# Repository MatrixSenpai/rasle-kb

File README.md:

# Rasle-KB

A [Sofle Choc](https://github.com/josefadamcik/SofleKeyboard) inspired keyboard featuring a 6x4+5 staggered key layout with onboard RP2040 MCU.

## Features:
- Onboard RP2040
- Per-Switch LED backlighting
- [Japanese Duplex Matrix](https://kbd.news/The-Japanese-duplex-matrix-1391.html) design
- RST/BootSel switches
- Onboard, accessible debug port
- Reversible design

Future features:
- Horizontal rotary encoder
- Display
- Wireless support + battery
- RP2350 variant

Planned support for QMK + ZMK, with first-party support for custom, developer-written firmware based on [Embassy](https://embassy.dev/)

Hardware and PCB design is licensed under CC BY-NC-SA. Firmware, software, and any additional non-hardware components are licensed under GNU GPLv3.

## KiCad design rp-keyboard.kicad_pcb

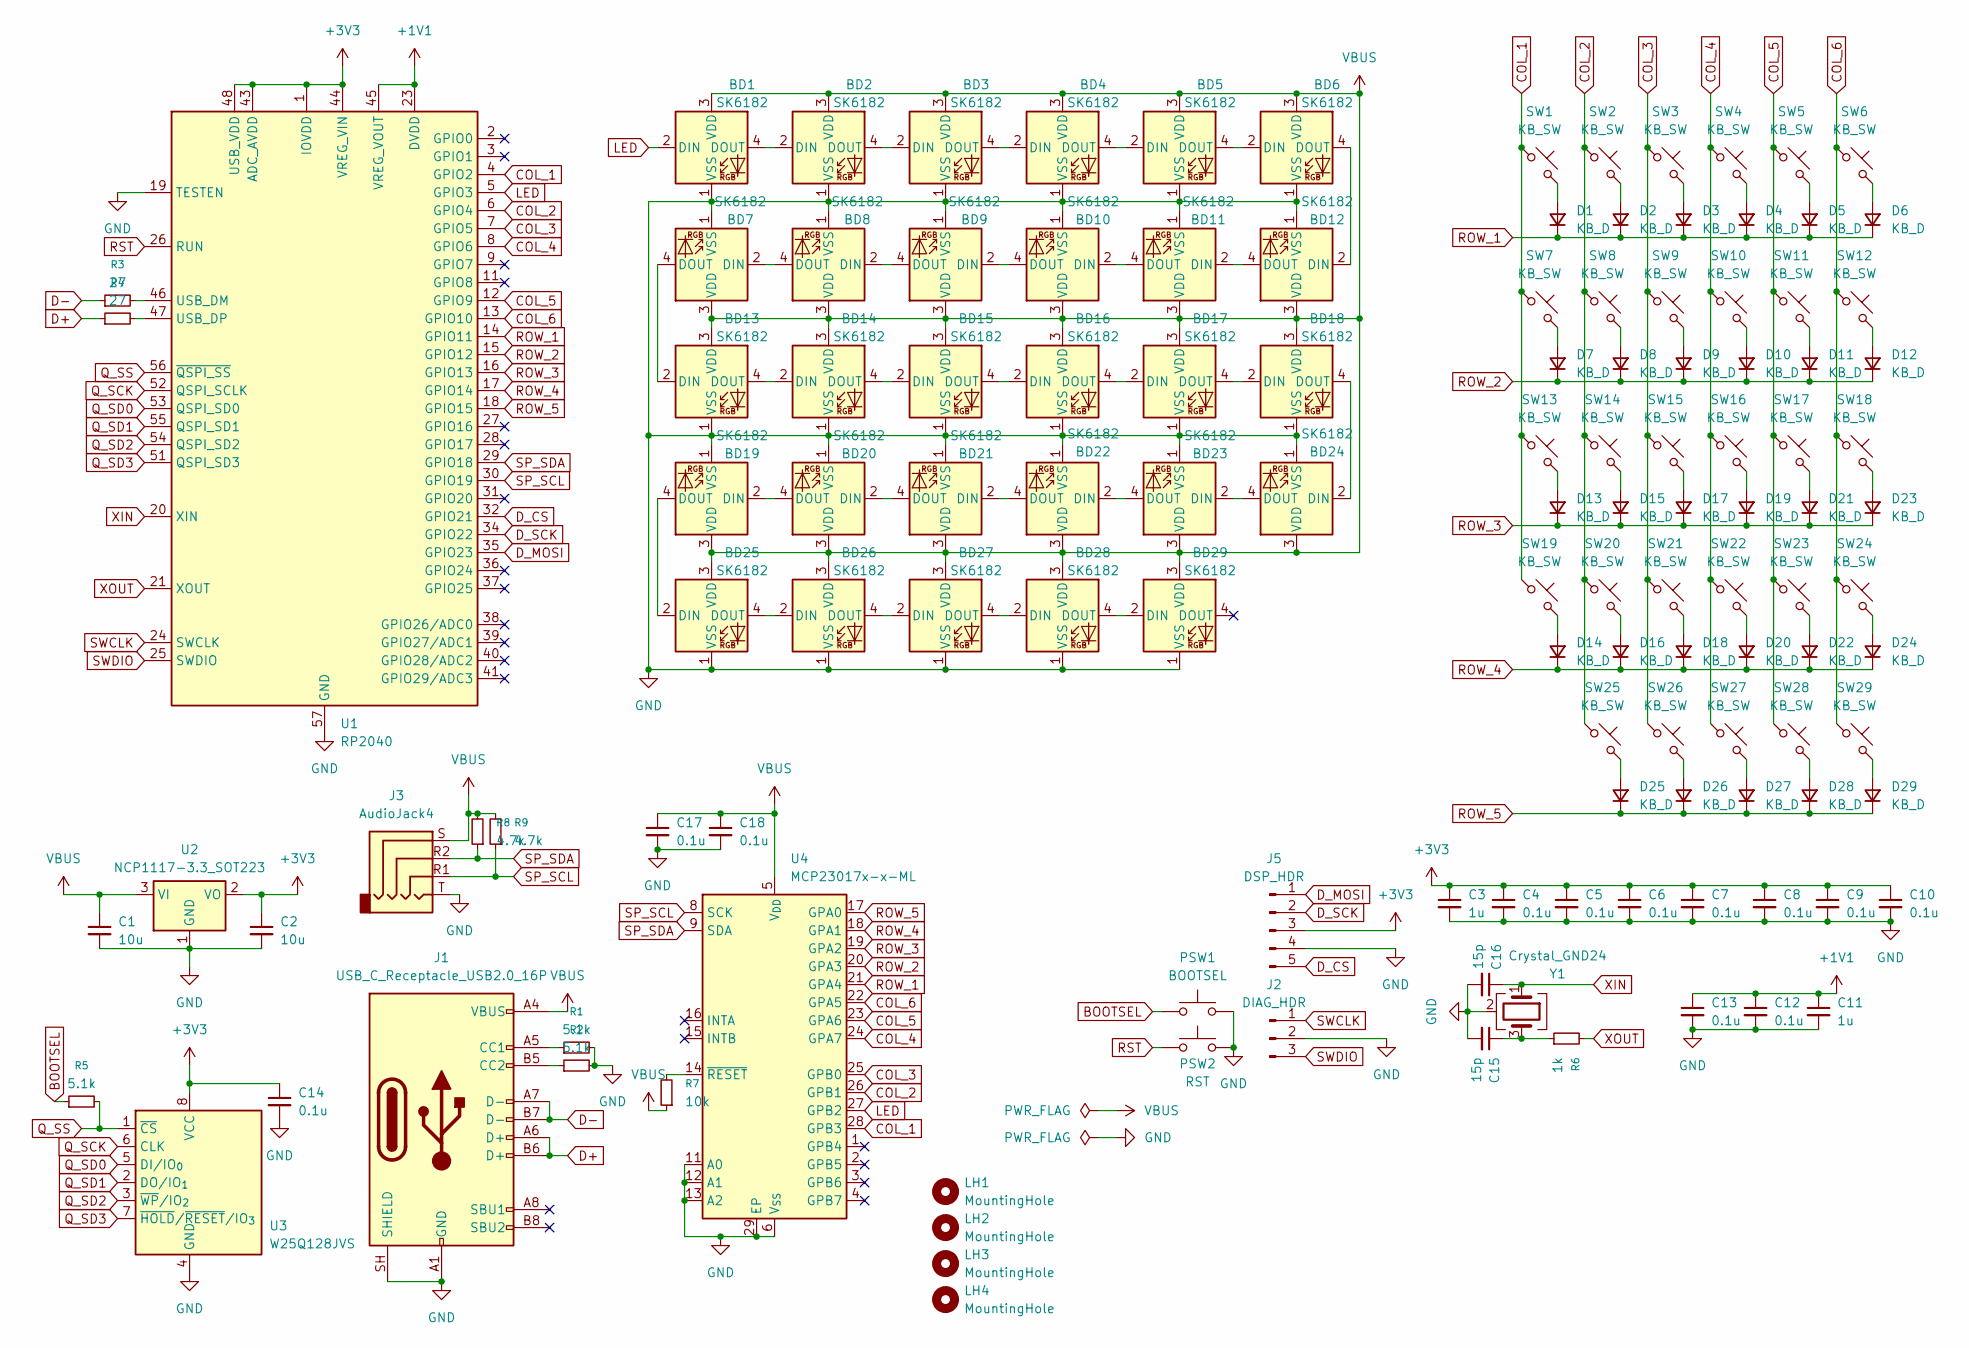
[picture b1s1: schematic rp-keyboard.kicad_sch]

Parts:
BD1, BD2, BD3, BD4, BD5, BD6, BD7, BD8, BD9, BD10, BD11, BD12, BD13, BD14, BD15, BD16, BD17, BD18, BD19, BD20, BD21, BD22, BD23, BD24, BD25, BD26, BD27, BD28, BD29: SK6182; LED_SK6812MINI-E_3.2x2.8mm_P1.5mm_ReverseMount Reversible
C1, C2: 10u; C_0402_1005Metric_Pad0.74x0.62mm_HandSolder
C3, C11: 1u; C_0402_1005Metric_Pad0.74x0.62mm_HandSolder
C4, C5, C6, C7, C8, C9, C10, C12, C13, C14, C17, C18: 0.1u; C_0402_1005Metric_Pad0.74x0.62mm_HandSolder
C15, C16: 15p; C_0402_1005Metric_Pad0.74x0.62mm_HandSolder
D1, D2, D3, D4, D5, D6, D7, D8, D9, D10, D11, D12, D13, D14, D15, D16, D17, D18, D19, D20, D21, D22, D23, D24, D25, D26, D27, D28, D29: KB_D; D_SOD-123 Reversible
J1: USB_C_Receptacle_USB2.0_16P; USB_C_Receptacle_HRO_TYPE-C-31-M-12
J2: DIAG_HDR; PinHeader_1x03_P2.54mm_Vertical
J3: AudioJack4; Jack_3.5mm_KoreanHropartsElec_PJ-320D-4A_Horizontal
J5: DSP_HDR; PinHeader_1x05_P2.54mm_Vertical
LH1, LH2, LH3, LH4: MountingHole; MountingHole_4.3mm_M4
PSW1: BOOTSEL; SW_SPST_SKQG_WithStem
PSW2: RST; SW_SPST_SKQG_WithStem
R1, R2, R5: 5.1k; R_0402_1005Metric_Pad0.72x0.64mm_HandSolder
R3, R4: 27; R_0402_1005Metric_Pad0.72x0.64mm_HandSolder
R6: 1k; R_0402_1005Metric_Pad0.72x0.64mm_HandSolder
R7: 10k; R_0402_1005Metric_Pad0.72x0.64mm_HandSolder
R8, R9: 4.7k; R_0402_1005Metric_Pad0.72x0.64mm_HandSolder
SW1, SW2, SW3, SW4, SW5, SW6, SW7, SW8, SW9, SW10, SW11, SW12, SW13, SW14, SW15, SW16, SW17, SW18, SW19, SW20, SW21, SW22, SW23, SW24, SW25, SW26, SW27, SW28, SW29: KB_SW; SW_Hotswap_Kailh_Choc_V1V2_1.00u Reversible
U1: RP2040; QFN-56-1EP_7x7mm_P0.4mm_EP3.2x3.2mm
U2: NCP1117-3.3_SOT223; SOT-223-3_TabPin2
U3: W25Q128JVS; SOIC-8_5.3x5.3mm_P1.27mm
U4: MCP23017x-x-ML; QFN-28-1EP_6x6mm_P0.65mm_EP4.25x4.25mm
Y1: Crystal_GND24; Crystal_SMD_Abracon_ABM8G-4Pin_3.2x2.5mm

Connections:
+1V1: C11.1, C12.1, C13.1, U1.23 (DVDD), U1.45 (VREG_VOUT), U1.50 (DVDD)
+3V3: C2.1, C3.1, C4.1, C5.1, C6.1, C7.1, C8.1, C9.1, C10.1, C14.1, J5.3, U1.1 (IOVDD), U1.10 (IOVDD), U1.22 (IOVDD), U1.33 (IOVDD), U1.42 (IOVDD), U1.43 (ADC_AVDD), U1.44 (VREG_VIN), U1.48 (USB_VDD), U1.49 (IOVDD), U2.2 (VO), U3.8 (VCC)
BOOTSEL: PSW1.1, R5.1
COL_1: SW1.1, SW7.1, SW13.1, SW19.1, U1.4 (GPIO2), U4.28 (GPB3)
COL_2: SW2.1, SW8.1, SW14.1, SW20.1, SW25.1, U1.6 (GPIO4), U4.26 (GPB1)
COL_3: SW3.1, SW9.1, SW15.1, SW21.1, SW26.1, U1.7 (GPIO5), U4.25 (GPB0)
COL_4: SW4.1, SW10.1, SW16.1, SW22.1, SW27.1, U1.8 (GPIO6), U4.24 (GPA7)
COL_5: SW5.1, SW11.1, SW17.1, SW23.1, SW28.1, U1.12 (GPIO9), U4.23 (GPA6)
COL_6: SW6.1, SW12.1, SW18.1, SW24.1, SW29.1, U1.13 (GPIO10), U4.22 (GPA5)
D+: J1.A6 (D+), J1.B6 (D+), R4.1
D-: J1.A7 (D-), J1.B7 (D-), R3.1
D_CS: J5.5, U1.32 (GPIO21)
D_MOSI: J5.1, U1.35 (GPIO23)
D_SCK: J5.2, U1.34 (GPIO22)
GND: BD1.1 (VSS), BD2.1 (VSS), BD3.1 (VSS), BD4.1 (VSS), BD5.1 (VSS), BD6.1 (VSS), BD7.1 (VSS), BD8.1 (VSS), BD9.1 (VSS), BD10.1 (VSS), BD11.1 (VSS), BD12.1 (VSS), BD13.1 (VSS), BD14.1 (VSS), BD15.1 (VSS), BD16.1 (VSS), BD17.1 (VSS), BD18.1 (VSS), BD19.1 (VSS), BD20.1 (VSS), BD21.1 (VSS), BD22.1 (VSS), BD23.1 (VSS), BD24.1 (VSS), BD25.1 (VSS), BD26.1 (VSS), BD27.1 (VSS), BD28.1 (VSS), BD29.1 (VSS), C1.2, C2.2, C3.2, C4.2, C5.2, C6.2, C7.2, C8.2, C9.2, C10.2, C11.2, C12.2, C13.2, C14.2, C15.2, C16.2, C17.2, C18.2, J1.A1 (GND), J1.A12 (GND), J1.B1 (GND), J1.B12 (GND), J1.SH (SHIELD), J2.2, J3.T, J5.4, PSW1.2, PSW2.2, R1.2, R2.2, U1.19 (TESTEN), U1.57 (GND), U2.1 (GND), U3.4 (GND), U4.6 (V_{SS}), U4.11 (A0), U4.12 (A1), U4.13 (A2), U4.29 (EP), Y1.2 (G), Y1.4 (G)
LED: BD1.2 (DIN), U1.5 (GPIO3), U4.27 (GPB2)
unnamed: BD1.4 (DOUT), BD2.2 (DIN)
unnamed: BD2.4 (DOUT), BD3.2 (DIN)
unnamed: BD3.4 (DOUT), BD4.2 (DIN)
unnamed: BD4.4 (DOUT), BD5.2 (DIN)
unnamed: BD5.4 (DOUT), BD6.2 (DIN)
unnamed: BD7.2 (DIN), BD8.4 (DOUT)
unnamed: BD8.2 (DIN), BD9.4 (DOUT)
unnamed: BD10.2 (DIN), BD11.4 (DOUT)
unnamed: BD9.2 (DIN), BD10.4 (DOUT)
unnamed: BD11.2 (DIN), BD12.4 (DOUT)
unnamed: BD6.4 (DOUT), BD12.2 (DIN)
unnamed: BD7.4 (DOUT), BD13.2 (DIN)
unnamed: BD13.4 (DOUT), BD14.2 (DIN)
unnamed: BD14.4 (DOUT), BD15.2 (DIN)
unnamed: BD15.4 (DOUT), BD16.2 (DIN)
unnamed: BD16.4 (DOUT), BD17.2 (DIN)
unnamed: BD17.4 (DOUT), BD18.2 (DIN)
unnamed: BD18.4 (DOUT), BD24.2 (DIN)
unnamed: BD19.2 (DIN), BD20.4 (DOUT)
unnamed: BD19.4 (DOUT), BD25.2 (DIN)
unnamed: BD20.2 (DIN), BD21.4 (DOUT)
unnamed: BD21.2 (DIN), BD22.4 (DOUT)
unnamed: BD22.2 (DIN), BD23.4 (DOUT)
unnamed: BD23.2 (DIN), BD24.4 (DOUT)
unnamed: BD25.4 (DOUT), BD26.2 (DIN)
unnamed: BD26.4 (DOUT), BD27.2 (DIN)
unnamed: BD27.4 (DOUT), BD28.2 (DIN)
unnamed: BD28.4 (DOUT), BD29.2 (DIN)
unnamed: C15.1, R6.1, Y1.3
unnamed: D1.2 (A), SW1.2
unnamed: D2.2 (A), SW2.2
unnamed: D3.2 (A), SW3.2
unnamed: D4.2 (A), SW4.2
unnamed: D5.2 (A), SW5.2
unnamed: D6.2 (A), SW6.2
unnamed: D7.2 (A), SW7.2
unnamed: D8.2 (A), SW8.2
unnamed: D9.2 (A), SW9.2
unnamed: D10.2 (A), SW10.2
unnamed: D11.2 (A), SW11.2
unnamed: D12.2 (A), SW12.2
unnamed: D13.2 (A), SW13.2
unnamed: D14.2 (A), SW19.2
unnamed: D15.2 (A), SW14.2
unnamed: D16.2 (A), SW20.2
unnamed: D17.2 (A), SW15.2
unnamed: D18.2 (A), SW21.2
unnamed: D19.2 (A), SW16.2
unnamed: D20.2 (A), SW22.2
unnamed: D21.2 (A), SW17.2
unnamed: D22.2 (A), SW23.2
unnamed: D23.2 (A), SW18.2
unnamed: D24.2 (A), SW24.2
unnamed: D25.2 (A), SW25.2
unnamed: D26.2 (A), SW26.2
unnamed: D27.2 (A), SW27.2
unnamed: D28.2 (A), SW28.2
unnamed: D29.2 (A), SW29.2
unnamed: J1.A5 (CC1), R1.1
unnamed: J1.B5 (CC2), R2.1
unnamed: R3.2, U1.46 (USB_DM)
unnamed: R4.2, U1.47 (USB_DP)
unnamed: R7.2, U4.14 (~RESET)
Q_SCK: U1.52 (QSPI_SCLK), U3.6 (CLK)
Q_SD0: U1.53 (QSPI_SD0), U3.5 (DI/IO_{0})
Q_SD1: U1.55 (QSPI_SD1), U3.2 (DO/IO_{1})
Q_SD2: U1.54 (QSPI_SD2), U3.3 (~WP/IO_{2})
Q_SD3: U1.51 (QSPI_SD3), U3.7 (~HOLD/~RESET/IO_{3})
Q_SS: R5.2, U1.56 (~QSPI_SS), U3.1 (~CS)
ROW_1: D1.1 (K), D2.1 (K), D3.1 (K), D4.1 (K), D5.1 (K), D6.1 (K), U1.14 (GPIO11), U4.21 (GPA4)
ROW_2: D7.1 (K), D8.1 (K), D9.1 (K), D10.1 (K), D11.1 (K), D12.1 (K), U1.15 (GPIO12), U4.20 (GPA3)
ROW_3: D13.1 (K), D15.1 (K), D17.1 (K), D19.1 (K), D21.1 (K), D23.1 (K), U1.16 (GPIO13), U4.19 (GPA2)
ROW_4: D14.1 (K), D16.1 (K), D18.1 (K), D20.1 (K), D22.1 (K), D24.1 (K), U1.17 (GPIO14), U4.18 (GPA1)
ROW_5: D25.1 (K), D26.1 (K), D27.1 (K), D28.1 (K), D29.1 (K), U1.18 (GPIO15), U4.17 (GPA0)
RST: PSW2.1, U1.26 (RUN)
SP_SCL: J3.R1, R9.1, U1.30 (GPIO19), U4.8 (SCK)
SP_SDA: J3.R2, R8.1, U1.29 (GPIO18), U4.9 (SDA)
SWCLK: J2.1, U1.24 (SWCLK)
SWDIO: J2.3, U1.25 (SWDIO)
VBUS: BD1.3 (VDD), BD2.3 (VDD), BD3.3 (VDD), BD4.3 (VDD), BD5.3 (VDD), BD6.3 (VDD), BD7.3 (VDD), BD8.3 (VDD), BD9.3 (VDD), BD10.3 (VDD), BD11.3 (VDD), BD12.3 (VDD), BD13.3 (VDD), BD14.3 (VDD), BD15.3 (VDD), BD16.3 (VDD), BD17.3 (VDD), BD18.3 (VDD), BD19.3 (VDD), BD20.3 (VDD), BD21.3 (VDD), BD22.3 (VDD), BD23.3 (VDD), BD24.3 (VDD), BD25.3 (VDD), BD26.3 (VDD), BD27.3 (VDD), BD28.3 (VDD), BD29.3 (VDD), C1.1, C17.1, C18.1, J1.A4 (VBUS), J1.A9 (VBUS), J1.B4 (VBUS), J1.B9 (VBUS), J3.S, R7.1, R8.2, R9.2, U2.3 (VI), U4.5 (V_{DD})
XIN: C16.1, U1.20 (XIN), Y1.1
XOUT: R6.2, U1.21 (XOUT)

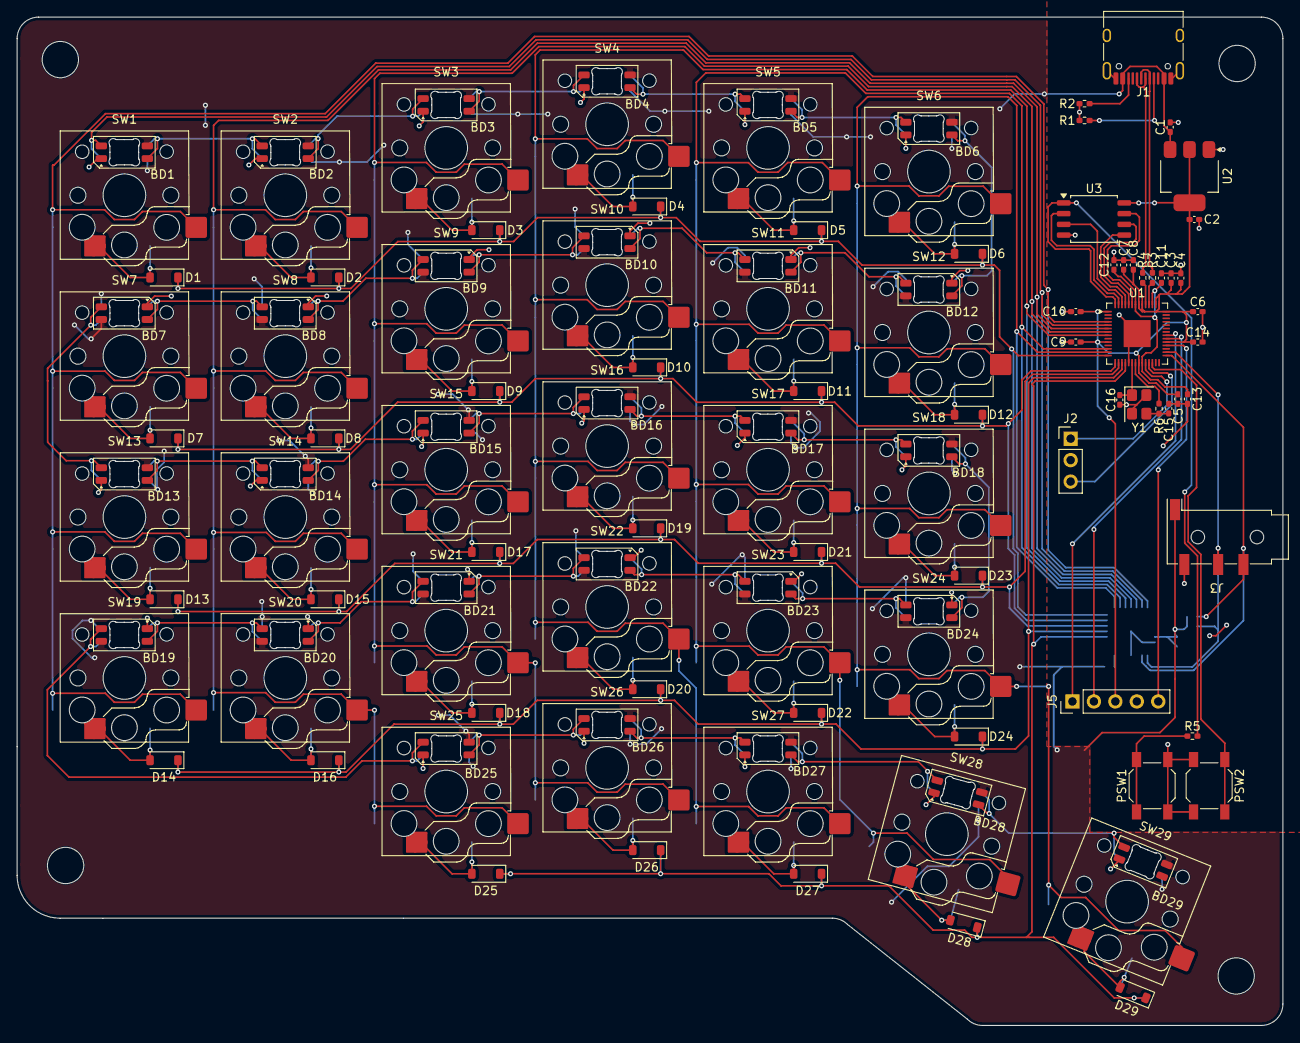
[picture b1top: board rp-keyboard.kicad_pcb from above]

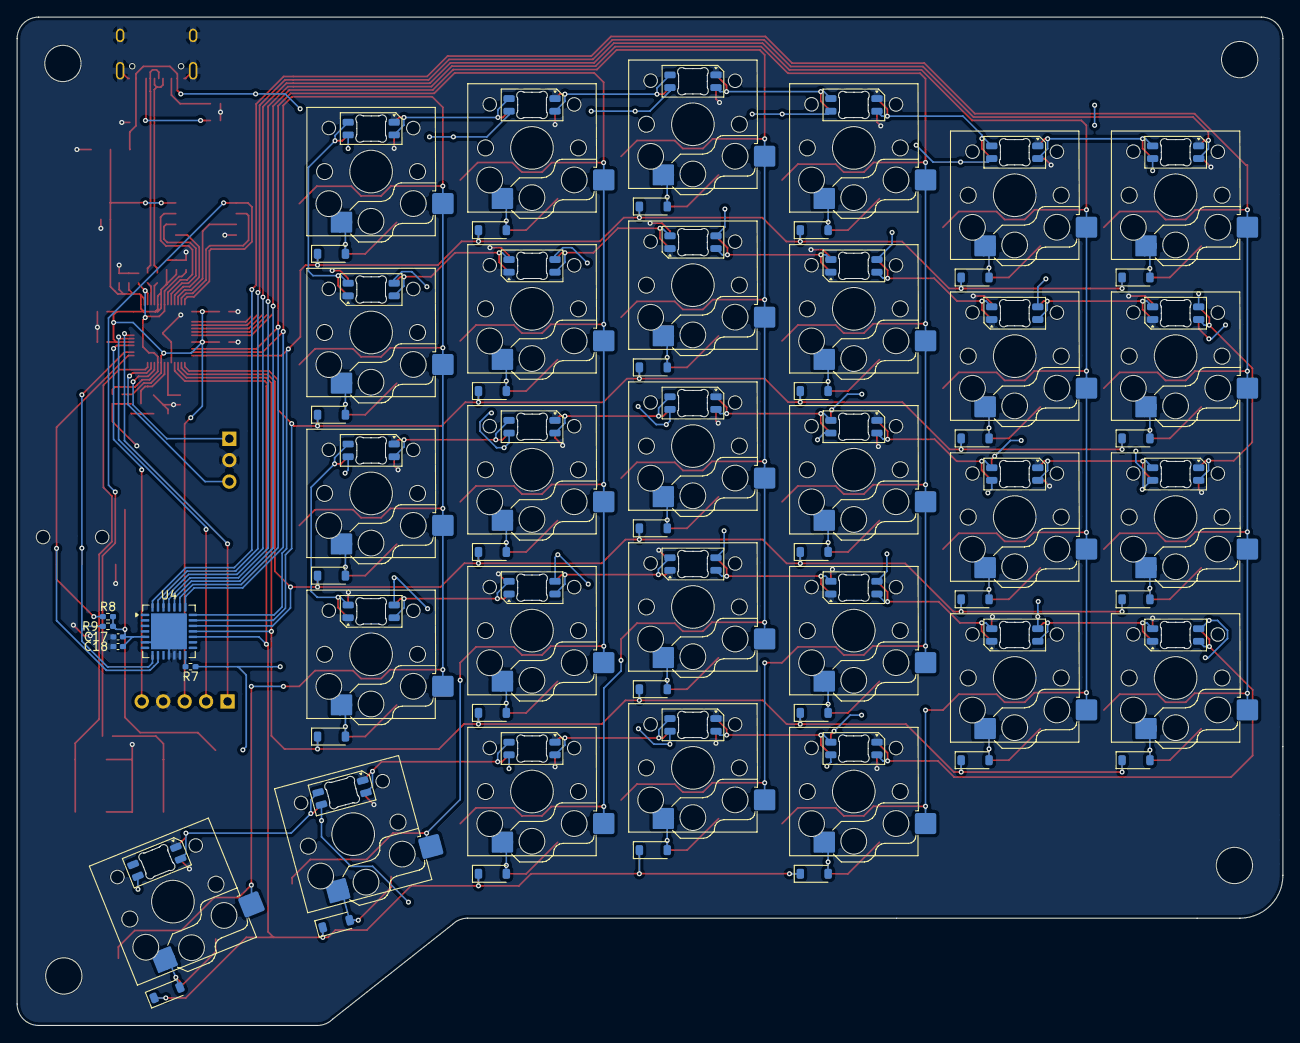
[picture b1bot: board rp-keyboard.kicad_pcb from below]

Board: 2 copper layers, 149.8 x 119.3 mm, 129 parts (6 on the bottom side), 98 nets.

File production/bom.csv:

Designator,Footprint,Quantity,Value,LCSC Part #
"BD1, BD10, BD11, BD12, BD13, BD14, BD15, BD16, BD17, BD18, BD19, BD2, BD20, BD21, BD22, BD23, BD24, BD25, BD26, BD27, BD28, BD29, BD3, BD4, BD5, BD6, BD7, BD8, BD9",LED_SK6812MINI-E_3.2x2.8mm_P1.5mm_ReverseMount Reversible,29,SK6182,
"C1, C2",0402,2,10u,
"C10, C12, C13, C14, C17, C18, C4, C5, C6, C7, C8, C9",0402,12,0.1u,
"C11, C3",0402,2,1u,
"C15, C16",0402,2,15p,
"D1, D10, D11, D12, D13, D14, D15, D16, D17, D18, D19, D2, D20, D21, D22, D23, D24, D25, D26, D27, D28, D29, D3, D4, D5, D6, D7, D8, D9",D_SOD-123 Reversible,29,KB_D,
J1,USB_C_Receptacle_HRO_TYPE-C-31-M-12,1,USB_C_Receptacle_USB2.0_16P,
J2,PinHeader_1x03_P2.54mm_Vertical,1,DIAG_HDR,
J3,Jack_3.5mm_KoreanHropartsElec_PJ-320D-4A_Horizontal,1,AudioJack4,
J5,PinHeader_1x05_P2.54mm_Vertical,1,DSP_HDR,
PSW1,SW_SPST_SKQG_WithStem,1,BOOTSEL,
PSW2,SW_SPST_SKQG_WithStem,1,RST,
"R1, R2, R5",0402,3,5.1k,
"R3, R4",0402,2,27,
R6,0402,1,1k,
R7,0402,1,10k,
"R8, R9",0402,2,4.7k,
"SW1, SW10, SW11, SW12, SW13, SW14, SW15, SW16, SW17, SW18, SW19, SW2, SW20, SW21, SW22, SW23, SW24, SW25, SW26, SW27, SW28, SW29, SW3, SW4, SW5, SW6, SW7, SW8, SW9",SW_Hotswap_Kailh_Choc_V1V2_1.00u Reversible,29,KB_SW,
U1,QFN-56-1EP_7x7mm_P0.4mm_EP3.2x3.2mm,1,RP2040,
U2,SOT-223-3_TabPin2,1,NCP1117-3.3_SOT223,
U3,SOIC-8_5.3x5.3mm_P1.27mm,1,W25Q128JVS,
U4,QFN-28-1EP_6x6mm_P0.65mm_EP4.25x4.25mm,1,MCP23017x-x-ML,
Y1,Crystal_SMD_Abracon_ABM8G-4Pin_3.2x2.5mm,1,Crystal_GND24,

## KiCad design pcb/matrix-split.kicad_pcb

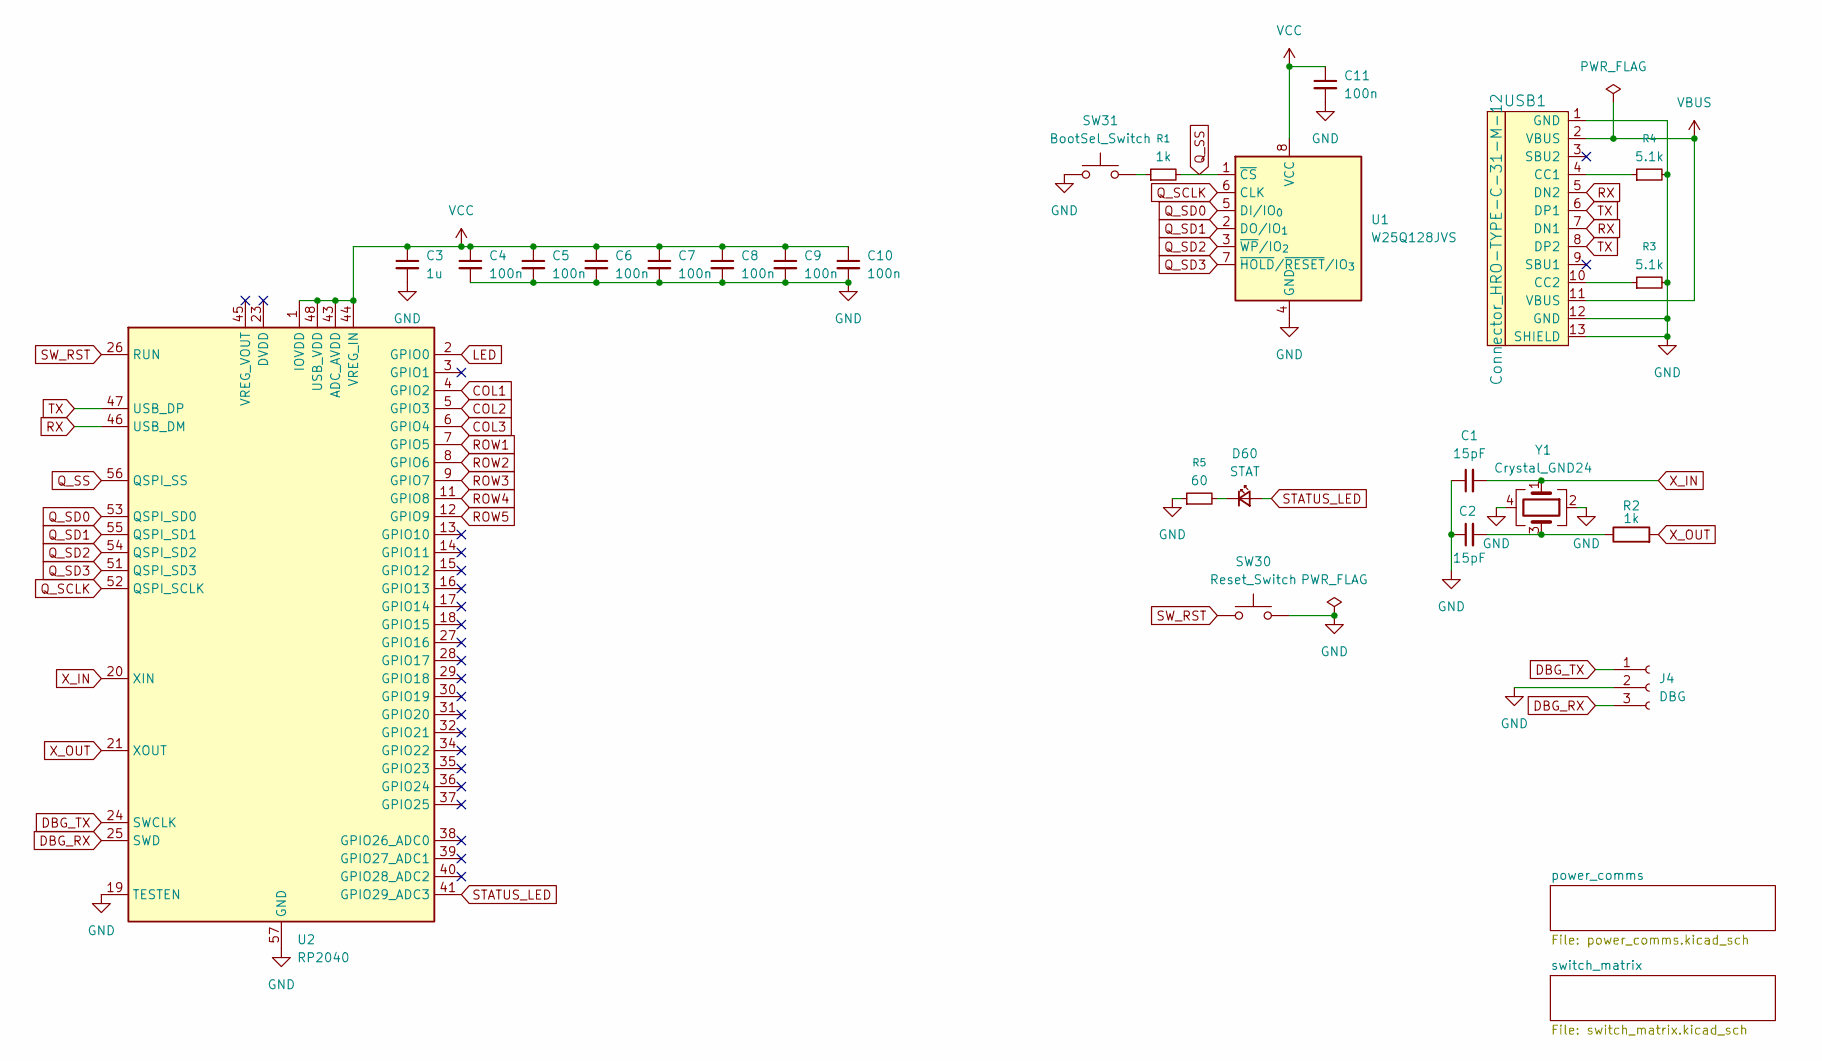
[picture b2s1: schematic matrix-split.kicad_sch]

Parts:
C1, C2: 15pF; C_0805_2012Metric
C3: 1u; C_0805_2012Metric
C4, C5, C6, C7, C8, C9, C10, C11: 100n; C_0805_2012Metric
D60: STAT; LED_0805_2012Metric
J4: DBG; PinHeader_1x03_P2.00mm_Vertical
R1, R2: 1k; R_0805_2012Metric
R3, R4: 5.1k; R_0805_2012Metric
R5: 60; R_0805_2012Metric
SW30: Reset_Switch; SW_SPST_TL3342
SW31: BootSel_Switch; SW_SPST_TL3342
U1: W25Q128JVS; SOIC-8_5.3x5.3mm_P1.27mm
U2: RP2040; QFN-56-1EP_7x7mm_P0.4mm_EP3.2x3.2mm
USB1: Connector_HRO-TYPE-C-31-M-12; HRO-TYPE-C-31-M-12-HandSoldering
Y1: Crystal_GND24; Crystal_SMD_Abracon_ABM8G-4Pin_3.2x2.5mm

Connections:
COL1: U2.4 (GPIO2); also elsewhere on the board
COL2: U2.5 (GPIO3); also elsewhere on the board
COL3: U2.6 (GPIO4); also elsewhere on the board
DBG_RX: J4.3, U2.25 (SWD)
DBG_TX: J4.1, U2.24 (SWCLK)
GND: C1.1, C2.1, C3.2, C4.2, C5.2, C6.2, C7.2, C8.2, C9.2, C10.2, C11.2, J4.2, R3.2, R4.2, R5.1, SW30.2, SW31.1, U1.4 (GND), U2.19 (TESTEN), U2.57 (GND), USB1.1 (GND), USB1.12 (GND), USB1.13 (SHIELD), Y1.2, Y1.4; also elsewhere on the board
LED: U2.2 (GPIO0); also elsewhere on the board
unnamed: C2.2, R2.1, Y1.3
unnamed: D60.1 (K), R5.2
unnamed: R1.1, SW31.2
unnamed: R4.1, USB1.4 (CC1)
unnamed: R3.1, USB1.10 (CC2)
Q_SCLK: U1.6 (CLK), U2.52 (QSPI_SCLK)
Q_SD0: U1.5 (DI/IO_{0}), U2.53 (QSPI_SD0)
Q_SD1: U1.2 (DO/IO_{1}), U2.55 (QSPI_SD1)
Q_SD2: U1.3 (~WP/IO_{2}), U2.54 (QSPI_SD2)
Q_SD3: U1.7 (~HOLD/~RESET/IO_{3}), U2.51 (QSPI_SD3)
Q_SS: R1.2, U1.1 (~CS), U2.56 (QSPI_SS)
ROW1: U2.7 (GPIO5); also elsewhere on the board
ROW2: U2.8 (GPIO6); also elsewhere on the board
ROW3: U2.9 (GPIO7); also elsewhere on the board
ROW4: U2.11 (GPIO8); also elsewhere on the board
ROW5: U2.12 (GPIO9); also elsewhere on the board
RX: U2.46 (USB_DM), USB1.5 (DN2), USB1.7 (DN1); also elsewhere on the board
STATUS_LED: D60.2 (A), U2.41 (GPIO29_ADC3)
SW_RST: SW30.1, U2.26 (RUN)
TX: U2.47 (USB_DP), USB1.6 (DP1), USB1.8 (DP2); also elsewhere on the board
VBUS: USB1.2 (VBUS), USB1.11 (VBUS); also elsewhere on the board
VCC: C3.1, C4.1, C5.1, C6.1, C7.1, C8.1, C9.1, C10.1, C11.1, U1.8 (VCC), U2.1 (IOVDD), U2.10 (IOVDD), U2.22 (IOVDD), U2.33 (IOVDD), U2.42 (IOVDD), U2.43 (ADC_AVDD), U2.44 (VREG_IN), U2.48 (USB_VDD), U2.49 (IOVDD); also elsewhere on the board
X_IN: C1.2, U2.20 (XIN), Y1.1
X_OUT: R2.2, U2.21 (XOUT)

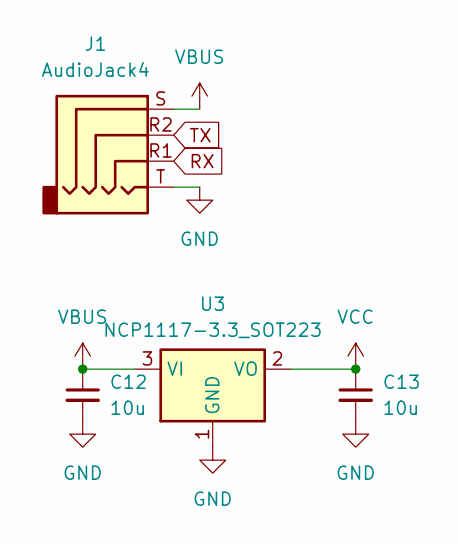
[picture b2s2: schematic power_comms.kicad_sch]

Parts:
C12, C13: 10u; C_0805_2012Metric
J1: AudioJack4; CON_MJ-4PP-9_Reversible
U3: NCP1117-3.3_SOT223; SOT-223-3_TabPin2

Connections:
GND: C12.2, C13.2, J1.T, U3.1 (GND); also elsewhere on the board
RX: J1.R1; also elsewhere on the board
TX: J1.R2; also elsewhere on the board
VBUS: C12.1, J1.S, U3.3 (VI); also elsewhere on the board
VCC: C13.1, U3.2 (VO); also elsewhere on the board

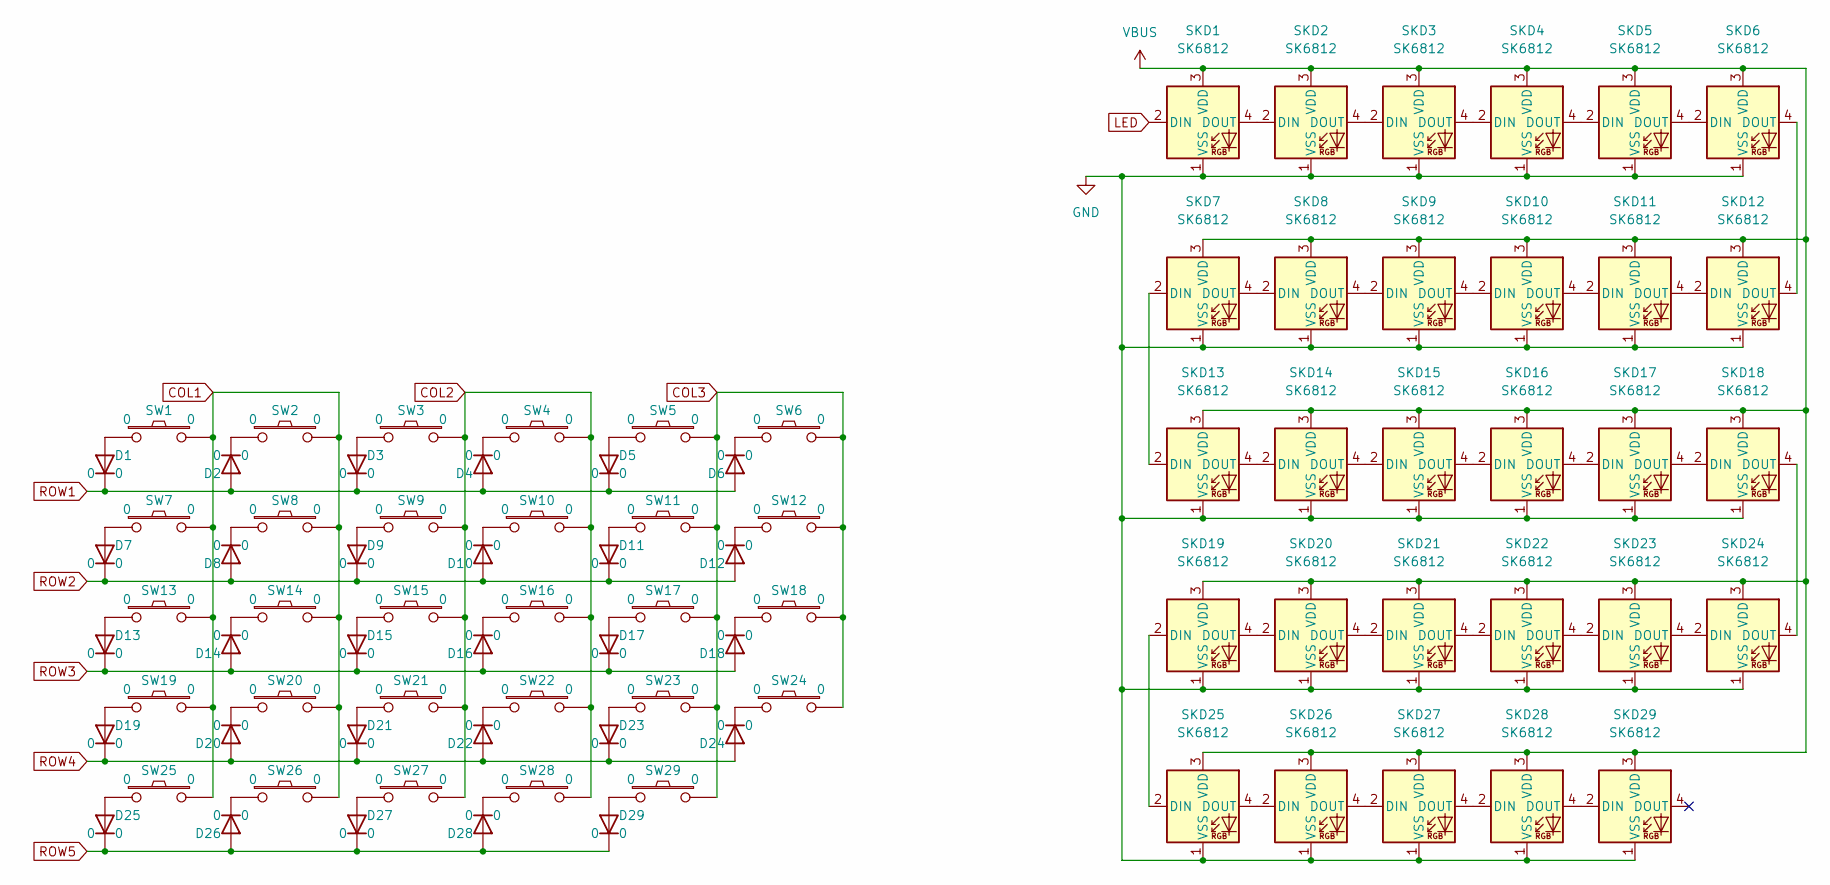
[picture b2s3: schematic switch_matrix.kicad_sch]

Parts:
D1, D2, D3, D4, D5, D6, D7, D8, D9, D10, D11, D12, D13, D14, D15, D16, D17, D18, D19, D20, D21, D22, D23, D24, D25, D26, D27, D28, D29: Diode; D_0805_2012Metric
SKD1, SKD2, SKD3, SKD4, SKD5, SKD6, SKD7, SKD8, SKD9, SKD10, SKD11, SKD12, SKD13, SKD14, SKD15, SKD16, SKD17, SKD18, SKD19, SKD20, SKD21, SKD22, SKD23, SKD24, SKD25, SKD26, SKD27, SKD28, SKD29: SK6812; LED_SK6812_PLCC4_5.0x5.0mm_P3.2mm
SW1, SW2, SW3, SW4, SW5, SW6, SW7, SW8, SW9, SW10, SW11, SW12, SW13, SW14, SW15, SW16, SW17, SW18, SW19, SW20, SW21, SW22, SW23, SW24, SW25, SW26, SW27, SW28, SW29: Switch; Kailh_socket_PG1350

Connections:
COL1: SW1.2, SW2.2, SW7.2, SW8.2, SW13.2, SW14.2, SW19.2, SW20.2, SW25.2, SW26.2; also elsewhere on the board
COL2: SW3.2, SW4.2, SW9.2, SW10.2, SW15.2, SW16.2, SW21.2, SW22.2, SW27.2, SW28.2; also elsewhere on the board
COL3: SW5.2, SW6.2, SW11.2, SW12.2, SW17.2, SW18.2, SW23.2, SW24.2, SW29.2; also elsewhere on the board
GND: SKD1.1 (VSS), SKD2.1 (VSS), SKD3.1 (VSS), SKD4.1 (VSS), SKD5.1 (VSS), SKD6.1 (VSS), SKD7.1 (VSS), SKD8.1 (VSS), SKD9.1 (VSS), SKD10.1 (VSS), SKD11.1 (VSS), SKD12.1 (VSS), SKD13.1 (VSS), SKD14.1 (VSS), SKD15.1 (VSS), SKD16.1 (VSS), SKD17.1 (VSS), SKD18.1 (VSS), SKD19.1 (VSS), SKD20.1 (VSS), SKD21.1 (VSS), SKD22.1 (VSS), SKD23.1 (VSS), SKD24.1 (VSS), SKD25.1 (VSS), SKD26.1 (VSS), SKD27.1 (VSS), SKD28.1 (VSS), SKD29.1 (VSS); also elsewhere on the board
LED: SKD1.2 (DIN); also elsewhere on the board
unnamed: D1.2 (A), SW1.1
unnamed: D2.1 (K), SW2.1
unnamed: D3.2 (A), SW3.1
unnamed: D4.1 (K), SW4.1
unnamed: D5.2 (A), SW5.1
unnamed: D6.1 (K), SW6.1
unnamed: D7.2 (A), SW7.1
unnamed: D8.1 (K), SW8.1
unnamed: D9.2 (A), SW9.1
unnamed: D10.1 (K), SW10.1
unnamed: D11.2 (A), SW11.1
unnamed: D12.1 (K), SW12.1
unnamed: D13.2 (A), SW13.1
unnamed: D14.1 (K), SW14.1
unnamed: D15.2 (A), SW15.1
unnamed: D16.1 (K), SW16.1
unnamed: D17.2 (A), SW17.1
unnamed: D18.1 (K), SW18.1
unnamed: D19.2 (A), SW19.1
unnamed: D20.1 (K), SW20.1
unnamed: D21.2 (A), SW21.1
unnamed: D22.1 (K), SW22.1
unnamed: D23.2 (A), SW23.1
unnamed: D24.1 (K), SW24.1
unnamed: D25.2 (A), SW25.1
unnamed: D26.1 (K), SW26.1
unnamed: D27.2 (A), SW27.1
unnamed: D28.1 (K), SW28.1
unnamed: D29.2 (A), SW29.1
unnamed: SKD1.4 (DOUT), SKD2.2 (DIN)
unnamed: SKD2.4 (DOUT), SKD3.2 (DIN)
unnamed: SKD3.4 (DOUT), SKD4.2 (DIN)
unnamed: SKD4.4 (DOUT), SKD5.2 (DIN)
unnamed: SKD5.4 (DOUT), SKD6.2 (DIN)
unnamed: SKD7.4 (DOUT), SKD8.2 (DIN)
unnamed: SKD8.4 (DOUT), SKD9.2 (DIN)
unnamed: SKD9.4 (DOUT), SKD10.2 (DIN)
unnamed: SKD10.4 (DOUT), SKD11.2 (DIN)
unnamed: SKD11.4 (DOUT), SKD12.2 (DIN)
unnamed: SKD6.4 (DOUT), SKD12.4 (DOUT)
unnamed: SKD7.2 (DIN), SKD13.2 (DIN)
unnamed: SKD13.4 (DOUT), SKD14.2 (DIN)
unnamed: SKD14.4 (DOUT), SKD15.2 (DIN)
unnamed: SKD15.4 (DOUT), SKD16.2 (DIN)
unnamed: SKD16.4 (DOUT), SKD17.2 (DIN)
unnamed: SKD17.4 (DOUT), SKD18.2 (DIN)
unnamed: SKD18.4 (DOUT), SKD24.4 (DOUT)
unnamed: SKD19.2 (DIN), SKD25.2 (DIN)
unnamed: SKD19.4 (DOUT), SKD20.2 (DIN)
unnamed: SKD20.4 (DOUT), SKD21.2 (DIN)
unnamed: SKD21.4 (DOUT), SKD22.2 (DIN)
unnamed: SKD22.4 (DOUT), SKD23.2 (DIN)
unnamed: SKD23.4 (DOUT), SKD24.2 (DIN)
unnamed: SKD25.4 (DOUT), SKD26.2 (DIN)
unnamed: SKD26.4 (DOUT), SKD27.2 (DIN)
unnamed: SKD27.4 (DOUT), SKD28.2 (DIN)
unnamed: SKD28.4 (DOUT), SKD29.2 (DIN)
ROW1: D1.1 (K), D2.2 (A), D3.1 (K), D4.2 (A), D5.1 (K), D6.2 (A); also elsewhere on the board
ROW2: D7.1 (K), D8.2 (A), D9.1 (K), D10.2 (A), D11.1 (K), D12.2 (A); also elsewhere on the board
ROW3: D13.1 (K), D14.2 (A), D15.1 (K), D16.2 (A), D17.1 (K), D18.2 (A); also elsewhere on the board
ROW4: D19.1 (K), D20.2 (A), D21.1 (K), D22.2 (A), D23.1 (K), D24.2 (A); also elsewhere on the board
ROW5: D25.1 (K), D26.2 (A), D27.1 (K), D28.2 (A), D29.1 (K); also elsewhere on the board
VBUS: SKD1.3 (VDD), SKD2.3 (VDD), SKD3.3 (VDD), SKD4.3 (VDD), SKD5.3 (VDD), SKD6.3 (VDD), SKD7.3 (VDD), SKD8.3 (VDD), SKD9.3 (VDD), SKD10.3 (VDD), SKD11.3 (VDD), SKD12.3 (VDD), SKD13.3 (VDD), SKD14.3 (VDD), SKD15.3 (VDD), SKD16.3 (VDD), SKD17.3 (VDD), SKD18.3 (VDD), SKD19.3 (VDD), SKD20.3 (VDD), SKD21.3 (VDD), SKD22.3 (VDD), SKD23.3 (VDD), SKD24.3 (VDD), SKD25.3 (VDD), SKD26.3 (VDD), SKD27.3 (VDD), SKD28.3 (VDD), SKD29.3 (VDD); also elsewhere on the board

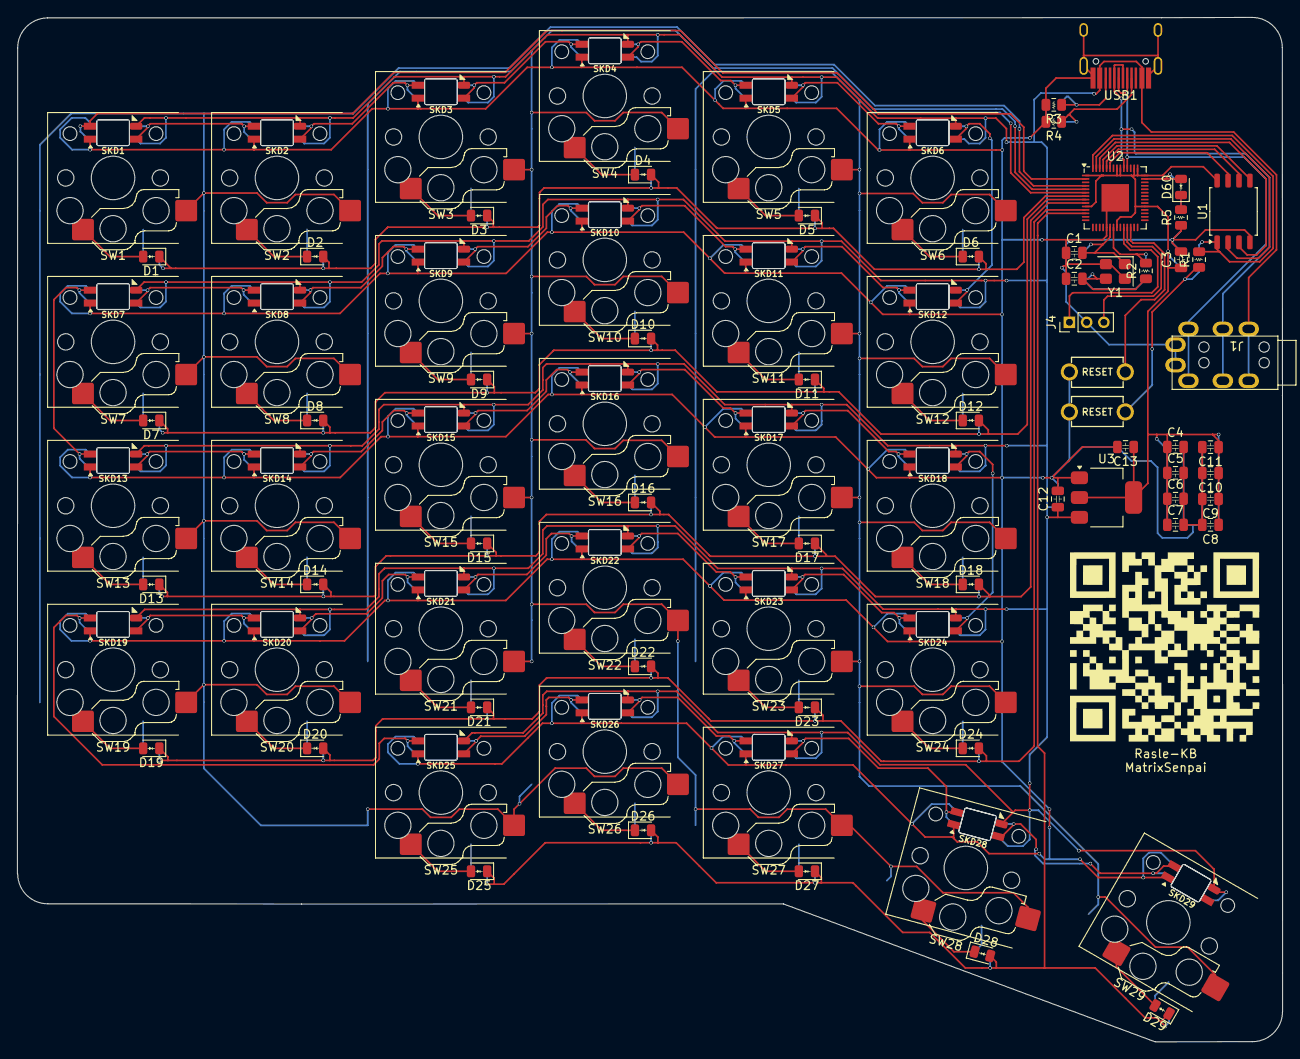
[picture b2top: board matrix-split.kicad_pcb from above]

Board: 2 copper layers, 147.0 x 119.0 mm, 115 parts (0 on the bottom side), 88 nets.

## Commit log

2025-08-08 updating routing and pcb layout
2025-08-11 making kb reversible
2025-08-11 adding licenses readme
2025-08-11 adding qr code and finalizing rev1
2025-08-13 working copy from publish
2026-06-08 ibom
